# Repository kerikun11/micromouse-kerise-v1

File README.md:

# MicroMouse KERISE v1

クラッシクサイズマイクロマウス

## 戦績

- 第37回全日本マイクロマウス大会2016
  - クラッシック競技フレッシュマンクラス予選10位
  - クラッシック競技フレッシュマンクラス決勝9位

## スペック

| 部品             | 型番            | 備考                    |
| :--------------- | :-------------- | :---------------------- |
| モーター         | 1717T006SR      | 17mm x 17mm             |
| エンコーダ       | IEH2-1024       | 1024パルス モーター直結 |
| マイコン         | STM32F405RG     | 168MHz                  |
| 赤外線LED        | VSLY5850        | 波長850mm 直径5mm       |
| フォトダイオード | SFH213FA        | 波長900nm 直径5mm       |
| モータードライバ | DRV8835         | 最大電流3A              |
| 6軸センサ        | MPU6500         | 3軸ジャイロ+3軸加速度   |
| バッテリー       | LG325-0120-1S-M | 3.7V 25C 120mAh 1S      |

## 回路設計

- KiCad

## 開発環境

- mbed RTOS

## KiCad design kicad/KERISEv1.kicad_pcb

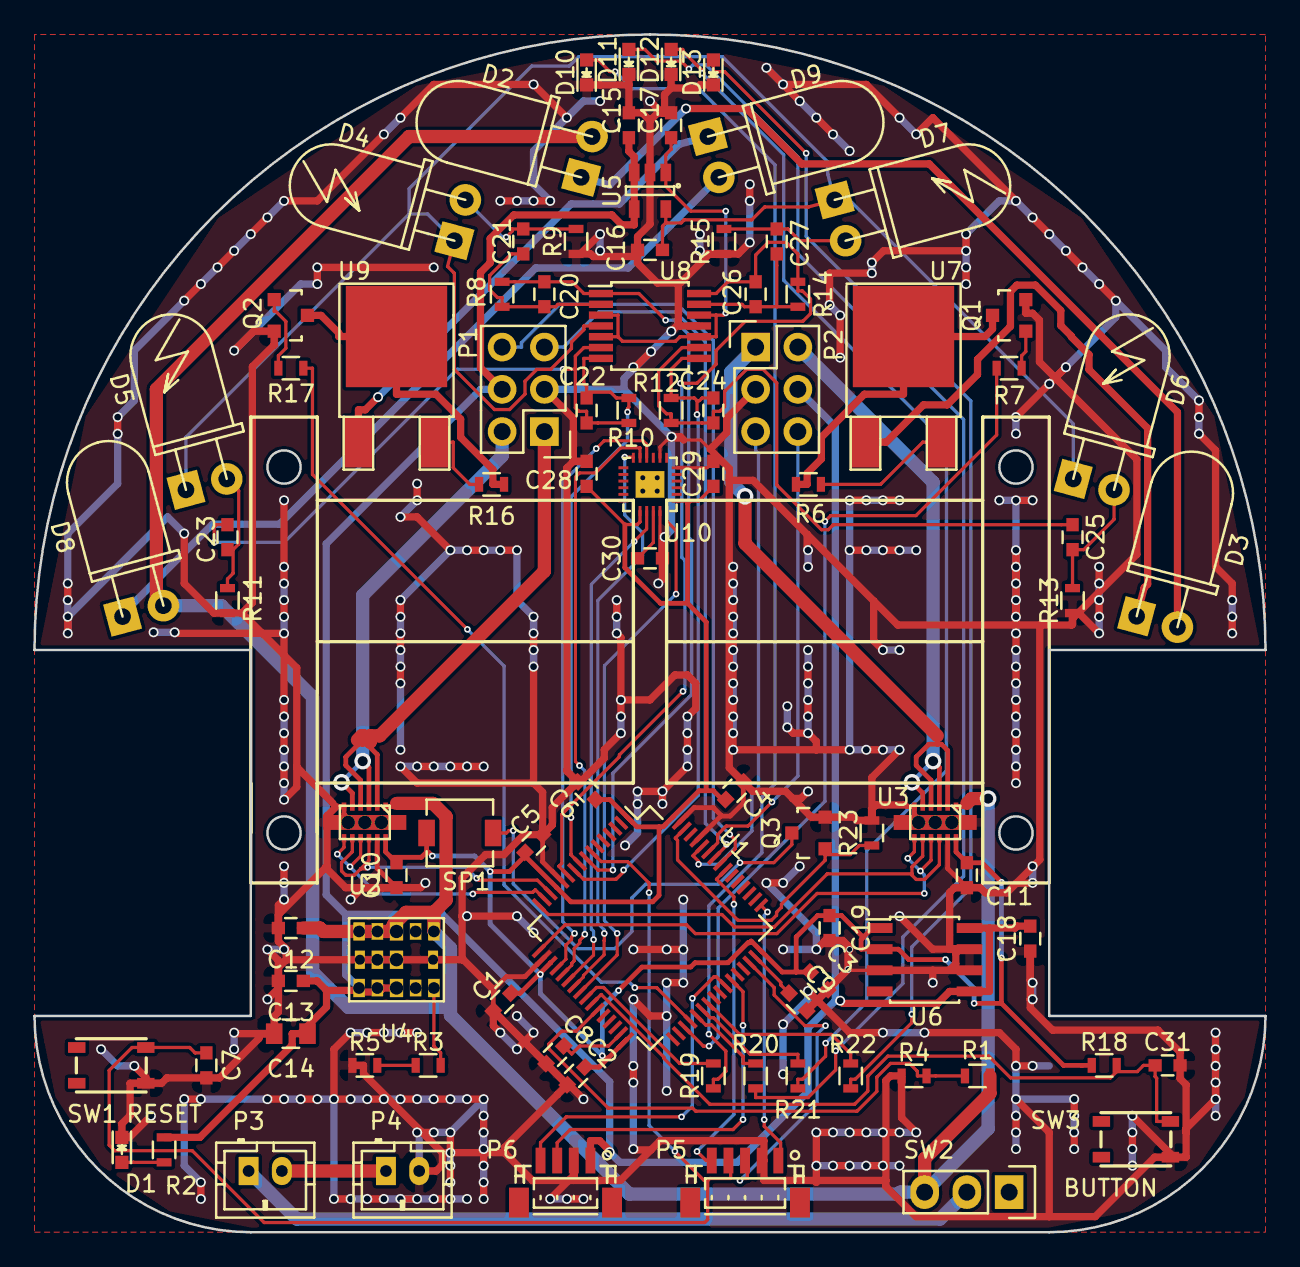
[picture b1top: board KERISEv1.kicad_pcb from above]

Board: 2 copper layers, 74.0 x 72.0 mm, 90 parts (0 on the bottom side), 73 nets.

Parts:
C1, C2, C3, C4, C5, C6, C7, C10, C11, C12, C13, C15, C18, C19, C29, C30, C31: 0.1u; C_0603
C8, C9: 2.2u; C_0603
C14: 22u; C_0805
C16, C17: 10u; C_0603
C20, C22, C24, C26: 22p; C_0603
C21, C23, C25, C27, C28: 0.01u; C_0603
D1: Power; LED_0603
D2, D3, D8, D9: VSLY5850; LED-5MM_Angle
D4, D5, D6, D7: SFH213FA; Photo-5MM_Angle
D10, D11, D12, D13: LED; LED_0603
P1, P2: MT-ENC; Pin_Header_Straight_2x03
P3: Battery_A; JST_PH_B2B-PH-K_02x2.00mm_Straight
P4: Battery_B; JST_PH_B2B-PH-K_02x2.00mm_Straight
P5: SWD; JST_SH_BM05B-SRSS-TB_05x1.00mm_Straight
P6: UART; JST_SH_BM04B-SRSS-TB_04x1.00mm_Straight
Q1, Q2: IRFML8244; SOT-23
Q3: BSS138; SOT-23
R1: 20k; R_0603
R2, R19, R20, R21, R22: 1k; R_0603
R3, R5: 68; R_0603
R4, R18: 10k; R_0603
R6, R16: 100; R_0603
R7, R17: 10; R_0603
R8, R10, R12, R14: 220k; R_0603
R9, R11, R13, R15: 100k; R_0603
R23: 4.7k; R_0603
SP1: SMT-0440; SMT-0440-S-R
SW1: RESET; SKRPACE010
SW2: Power; Pin_Header_Straight_1x03
SW3: BUTTON; SKRPACE010
U1: STM32F405RGTx; LQFP-64_10x10mm_Pitch0.5mm
U2, U3: DRV8835
U4: LXDC55FAAA-203
U5: REF1933; SOT-23-5
U6: LT1963ES8; SOIC-8_3.9x4.9mm_Pitch1.27mm
U7, U9: NSI45090; TO-252-2Lead
U8: AD8604; TSSOP-14_4.4x5mm_Pitch0.65mm
U10: MPU6500; QFN-24-1EP_3x3mm_Pitch0.4mm

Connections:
+1.65VA: C17.1, U5.1, U8.3, U8.5, U8.10, U8.12
+3.3VADC: C16.1, D4.1, D5.1, D6.1, D7.1, U5.5, U8.4
+3V3: C1.1, C2.1, C3.1, C4.1, C5.1, C6.1, C10.1, C11.1, C19.1, C28.1, C29.2, R18.1, SP1.1, U1.1, U1.13, U1.19, U1.32, U1.48, U1.64, U2.12, U3.12, U6.1, U6.2, U10.8, U10.13
+5V: C13.1, C14.1, C15.1, C18.1, P1.4, P2.4, P6.1, R2.1, U4.7, U4.8, U4.9, U5.3, U5.4, U6.5, U6.8
+BATT: C12.1, D2.2, D8.2, R1.1, SW2.3, U2.1, U3.1, U4.1, U4.3, U4.4, U4.5
/IR_LED_FL_SR/IR_LED_1: D8.1, D9.2
/IR_LED_FL_SR/IR_LED_2: D9.1, U9.1
/IR_LED_FL_SR/IR_LED_3: Q2.3, R16.1, U9.2
/IR_LED_SL_FR/IR_LED_1: D2.1, D3.2
/IR_LED_SL_FR/IR_LED_2: D3.1, U7.1
/IR_LED_SL_FR/IR_LED_3: Q1.3, R6.1, U7.2
/Motor_L/MT_OUT_1: P1.1, U2.2, U2.4
/Motor_L/MT_OUT_2: P1.2, U2.3, U2.5
/Motor_R/MT_OUT_1: P2.1, U3.2, U3.4
/Motor_R/MT_OUT_2: P2.2, U3.3, U3.5
AXIS_INT: U1.24, U10.12
AXIS_MISO: U1.22, U10.9
AXIS_MOSI: U1.23, U10.24
AXIS_SCK: U1.21, U10.23
AXIS_~CS: U1.20, U10.22
BAT-VOL: R1.2, R4.1, U1.27
BUTTON: C31.1, R18.2, SW3.2, U1.26
EN-L-A: P1.6, U1.56
EN-L-B: P1.5, U1.57
EN-R-A: P2.6, U1.58
EN-R-B: P2.5, U1.59
GND: C1.2, C2.2, C3.2, C4.2, C5.2, C6.2, C7.2, C8.2, C9.2, C10.2, C11.2, C12.2, C13.2, C14.2, C15.2, C16.2, C17.2, C18.2, C19.2, C28.2, C29.1, C30.2, C31.2, D1.1, D10.1, D11.1, D12.1, D13.1, P1.3, P2.3, P4.2, P5.2, P6.2, Q1.2, Q2.2, Q3.2, R4.2, R5.2, R9.2, R11.2, R13.2, R15.2, R23.2, SW1.4, SW3.4, U1.12, U1.18, U1.60, U1.63, U2.6, U2.11, U2.13, U3.6, U3.11, U3.13, U4.6, U4.12, U4.13, U4.14, U5.2, U6.3, U6.6, U6.7, U8.11, U10.11, U10.18, U10.20
LED_1: R19.1, U1.25
LED_2: R20.1, U1.37
LED_3: R21.1, U1.38
LED_4: R22.1, U1.39
MT-IN-L-1: U1.14, U2.8, U2.10
MT-IN-L-2: U1.15, U2.7, U2.9
MT-IN-R-1: U1.16, U3.8, U3.10
MT-IN-R-2: U1.17, U3.7, U3.9
unnamed: C8.1, U1.31
unnamed: C9.1, U1.47
unnamed: C20.2, C21.1, R8.2, U8.2
unnamed: C21.2, D4.2, R9.1
unnamed: C22.2, C23.1, R10.2, U8.6
unnamed: C23.2, D5.2, R11.1
unnamed: C24.2, C25.1, R12.2, U8.9
unnamed: C25.2, D6.2, R13.1
unnamed: C26.2, C27.1, R14.2, U8.13
unnamed: C27.2, D7.2, R15.1
unnamed: C30.1, U10.10
unnamed: D1.2, R2.2
unnamed: D10.2, R19.2
unnamed: D11.2, R20.2
unnamed: D12.2, R21.2
unnamed: D13.2, R22.2
unnamed: P3.1, SW2.2
unnamed: P3.2, P4.1
unnamed: Q1.1, R7.1
unnamed: Q2.1, R17.1
unnamed: Q3.3, SP1.2
unnamed: R3.1, R5.1
unnamed: R3.2, U4.11
unnamed: R6.2, U7.3
unnamed: R16.2, U9.3
PR-LED-FL_SR: R17.2, U1.36
PR-LED-SL-FR: R7.2, U1.35
PR-RCV-FL: C22.1, R10.1, U1.9, U8.7
PR-RCV-FR: C24.1, R12.1, U1.10, U8.8
PR-RCV-SL: C20.1, R8.1, U1.8, U8.1
PR-RCV-SR: C26.1, R14.1, U1.11, U8.14
RESET: C7.1, P5.4, SW1.2, U1.7
SPEAKER: Q3.1, R23.1, U1.62
SWCLK: P5.1, U1.49
SWDIO: P5.3, U1.46
SWO: P5.5, U1.55
UART-RX: P6.3, U1.43
UART-TX: P6.4, U1.42

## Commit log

2016-09-09 add kicad files
2016-09-09 ベタグランドの修正
    モータードライバの放熱効果を高めるために，サーマルリリーフをやめてベタ接続に．
2016-09-12 基板発注済ガーバーデータ
    1回目の基板発注
2016-09-12 MATLAB制御講習
    講習時のMATLAB
2016-09-12 Datasheets
    使用部品のデータシートと関連リンク
2020-05-02 Batteryチェックプログラムを実装
    起動時にチェック
2020-05-02 ジャイロとインターフェース
2020-05-02 mbedファームを追加
    mbed-cli環境
2020-05-02 モーター駆動プログラムを実装
    1kHzなのでうるさい．．．
2020-05-02 環境を再構築
    Makefileを追加．
2020-05-02 エンコーダを初期化
    newのせいで不定値になっていたのを修正
2020-05-02 ブザーとボタンを独立化
2020-05-02 部品表の追加
    xmlとcsv
2020-05-02 リフレクタの駆動プログラムの実装
    FFTはまだ．
2020-05-02 マウンタとホイールの3Dデータ
    20160917にDMM.makeに発注したデータ
2020-05-02 モーター
2020-05-02 CADデータの更新
2020-05-02 バッテリーのデータシート
2020-05-02 3D-CADデータの更新
2020-05-02 フォトリフレクタのFFTを実装，ブザーをOS化
2020-05-02 フットプリントを追加
2020-05-02 インスタンスはmain関数の最初で生成，BuzzerのRTOSを改良
2020-05-02 パラメータの調整
2020-05-02 軌道生成用のMATLABスクリプト
2020-05-02 移動不可能な方向にはエラーを出す
2020-05-02 直線の加減速も点追従
2020-05-02 速度制御器の実装
    エンコーダーのデータををもとにモーターを目標速度で走行させる．PIDパラメータはまだ．
2020-05-02 Rogyの迷路でパラメータ調整
2020-05-02 パラメータの調整，緊急停止
2020-05-02 誤差の修正方向が逆だった重大バグを修正
    前壁にぶつかる原因だった．
2020-05-02 とりあえずスラローム
    フィードフォワード&早すぎで全然動かない．
2020-05-02 バグを修正．
    かなりよくなった．
2020-05-02 シリアルによるラジコン
2020-05-02 スピード選択を実装，リセットせずに続けて走行
2020-05-02 横壁補正安定性の向上
2020-05-02 コメントを調整
2020-05-02 理科大迷路攻略
    10x10で探索途中でOperator new out of memory
2020-05-02 パラメータの調整
    行き過ぎて壁にぶつかる可能性あり
2020-05-02 MazeSolverのcppファイルをMakefileに追加
2020-05-02 インターフェースの調整
2020-05-02 sqrtの中身が負になるバグを修正
2020-05-02 前の壁を認識して垂直に止まる
2020-05-02 クラスとファイルの置き場所を調整
2020-05-02 停止位置は，x=60mm
2020-05-02 パラメータの調整
    加速度は4000mm/sに固定
2020-05-02 安定化．迷路探索可
2020-05-02 折り返すときに，通し角度の絶対値が大きくならない方向へ曲がる
2020-05-02 直線をより高速に
2020-05-02 壁と平行に走行
    壁があるかも判定し，ある場合は平行に走行
2020-05-02 最速走行でスタートへ戻る
2020-05-02 エンコーダによる並進位置のPID制御
2020-05-02 スラロームを高速化
    600mm/s
2020-05-02 安定性の向上
2020-05-02 停止位置の変更
    次のマスに頭を突っ込んだ状態から，完全に入った状態に変更
2020-05-02 安定したスラローム600m/s
2020-05-02 カエルの歌を実装...
2020-05-02 wall_avoidを座標変更へ
    角速度を変更するのではなく，y座標を調整する．
2020-05-02 MazeSolverのインタフェースを作成
    まだ途中
2020-05-02 本番環境で動いた
2020-05-02 MazeSolverを追加
    井土さんより頂いたプログラム
2020-05-02 MoveActionをQueueからMailに変更．
    複数アクションを連続してできるように．
2020-05-02 マスの移動プログラムを実装
    壁を見ながら
2020-05-02 カーブは等速円運動
    とりあえず動く
2020-05-02 EncoderMeasureとGyroMeasureは使わないので削除
2020-05-02 カーブはせずに，直進・回転・直進で曲がる
2020-05-02 迷路のテスト走行
2020-05-02 スタート時にしっかりゼロ補正
2020-05-02 外形の寸法の表示の修正
    76 mm => 74 mm
2020-05-02 各スレッドのスタックサイズを定義
2020-05-02 間欠データアップデート処理のRTOS化
2020-05-02 ログを見ながらPIDパラメータを調整
    実はI要素がほとんど働いていなかったことがわかった．
2020-05-02 最速走行が終了したら，スタートへ戻り，スピードを上げて再チャレ
    未動作検証．
2020-05-02 周波数成分抽出プログラムを追加
    井土さんより頂いたプログラム
2020-05-02 左右のスラローム実装
2020-05-02 MazeSolverと新アクションの調整
2020-05-02 リフレクタのキャリブレーションを実装
    スタートポジションの左右の壁でキャリブレーション
2020-05-02 400mm/sのスラロームを実装
    MATLABでクロソイド曲線の点列を作成し，それに追従する．
    実機確認済．
2020-05-02 軌道追従コードの一般化，左右実装
2020-05-02 迷路探索と最速走行の動作を切り分けて別々にアクセス
2020-05-02 アクションを選択するUIを作成
    エンコーダを利用
2020-05-02 クラスとファイルの置き場所の更新2
2020-05-02 区画の移動を座標で管理，誤差を次につなげる
2020-05-02 RETURNアクションを追加
    転回して，4cm前へ進む．
2020-05-02 区画の走行を安定化
    壁を利用
2020-05-02 優先順位を整理
2020-05-02 MPUのレジスタマップを追加
2020-05-02 横ずれ修正パラメータの調整
    未確認
2020-05-02 斜め走行
2020-05-02 フォトリフレクタのFFTを廃止，強さだけを読む
2020-05-02 途中から再開できるように修正
2020-05-02 MoveActionに開始と停止のスイッチを実装
2020-05-02 submodule add mbed-os-kerise
2020-05-02 180度ターンを生成，90度ターンも2パターン
2020-05-02 迷路全体の座標を右向きをx前向きをyとする．
2020-05-02 remove generated files
2020-05-02 KERISEv2から移植
2020-05-02 curve45Rのバグ修正
2020-05-02 MicroMouse2016から移植
2020-05-02 コードの改良
2020-05-02 絶対座標系で動作確認．
2020-05-02 KiCadデータの名前をKERISEv1に変更
2020-05-02 機体パラメータの更新(タイヤ径など)
2020-05-02 概形を作成
2020-05-02 4545用MATLABスクリプト
2020-05-02 小さな変更
2020-05-02 add kicad .gitignore
2020-05-02 MATLABで軌跡を改良
    なめらかに．
    角加速度と最大角速度を統一
2020-05-02 最速走行をひとつながりの点列の追従に．
    コードを大幅に変更
2020-05-02 回路図を修正
    電源スイッチにPchFETを挿入
    赤外線LED用FETのゲートをプルダウン
2020-05-02 探索走行のカーブを緩やかに
2020-05-02 fastRunのインターフェースを実装
2020-05-02 位置の積分を短冊積分から台形積分に変更
2020-05-02 add matlab .gitignore
2020-05-05 add README
2020-05-05 自己位置を推定せずに順次次の点に移る．
2020-05-05 サインカーブ加速の軌跡を生成
